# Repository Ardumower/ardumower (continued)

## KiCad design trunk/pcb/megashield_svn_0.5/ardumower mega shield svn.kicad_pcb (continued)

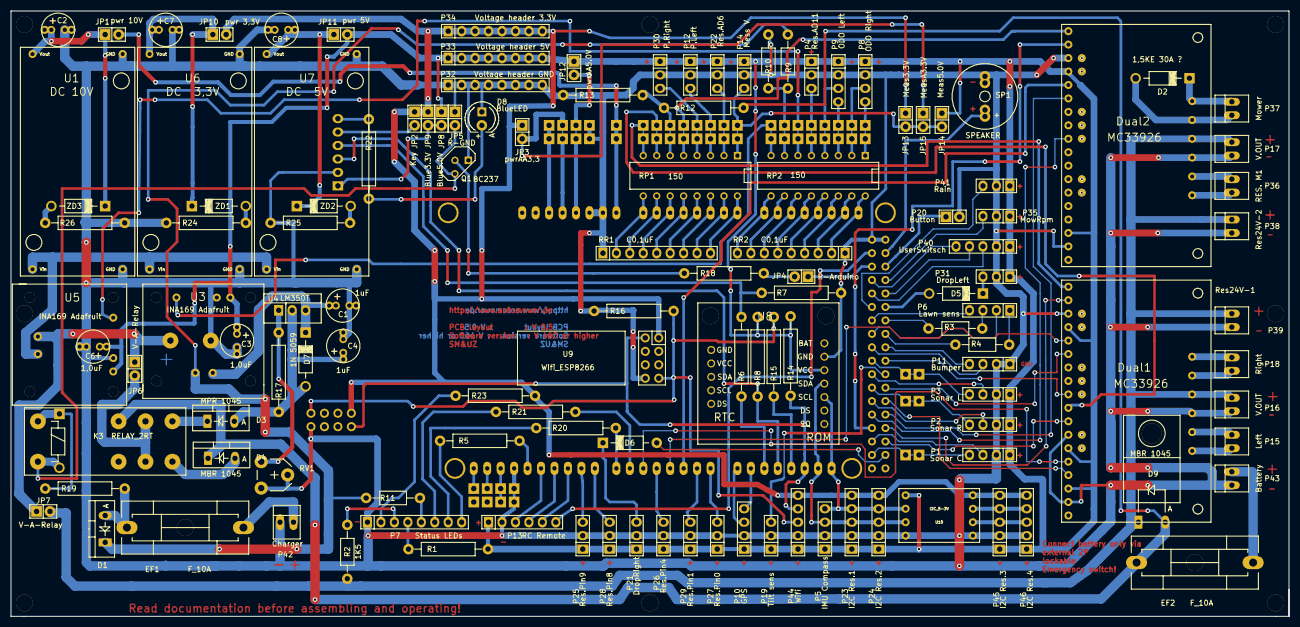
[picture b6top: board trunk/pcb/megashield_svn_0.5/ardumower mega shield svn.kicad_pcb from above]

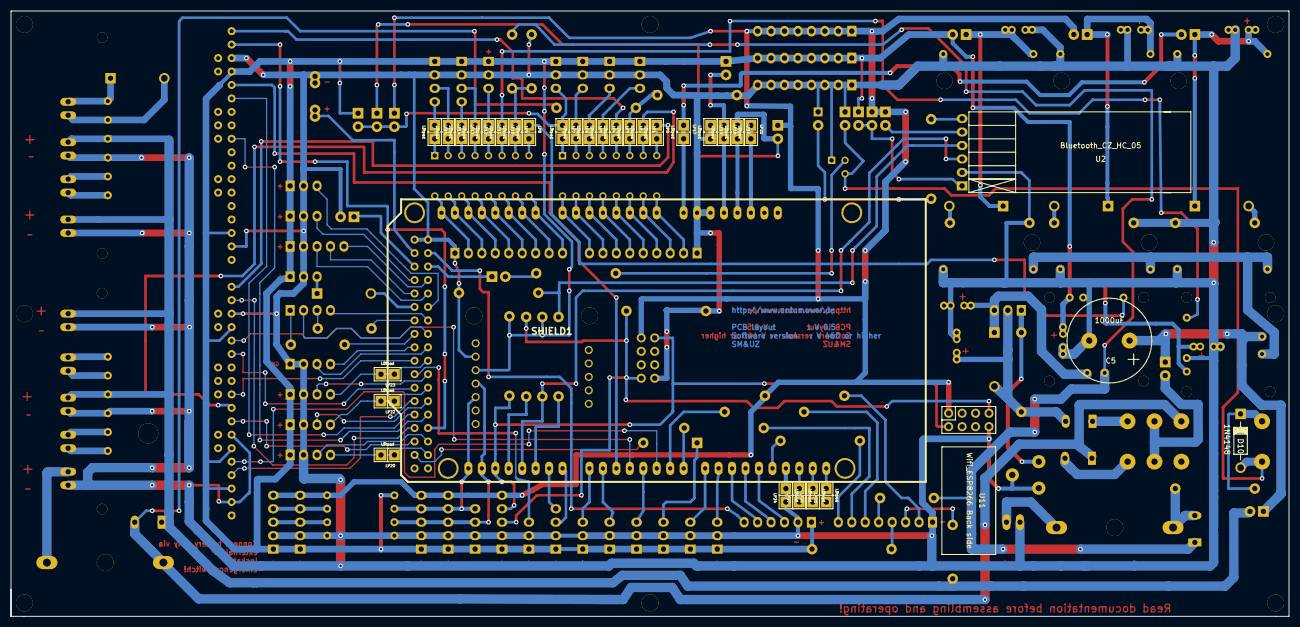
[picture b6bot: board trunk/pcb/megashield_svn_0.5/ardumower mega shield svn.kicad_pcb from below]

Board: 2 copper layers, 241.3 x 114.3 mm, 168 parts (33 on the bottom side), 147 nets.
